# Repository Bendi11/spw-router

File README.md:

# 8 Port SpaceWire Router
A hobby-grade [SpaceWire](https://www.esa.int/Enabling_Support/Space_Engineering_Technology/Onboard_Computers_and_Data_Handling/SpaceWire) router
aiming for full **ECSS-E-ST-50-12C** compliance utilizing a Xilinx Artix 7 FPGA.

## Hardware Development
KiCad schematics and board design files for the board are stored in the `hw/board` directory.
Custom footprints and 3D models are placed into the `hw/models` directory.

## FPGA
Verilog sources are located in the `rtl/src` directory, and both the synthesis and simulation
processes are managed by CMake.

Currently, the FPGA bitstream is generated with a fully open-source
[yosys](https://github.com/YosysHQ/yosys) + [nextpnr-xilinx](https://github.com/gatecat/nextpnr-xilinx) flow,
and does not require the Xilinx Vivado software.
Paths to the required tools must currently be provided in an `env.cmake` file located in the
`rtl/cmake` directory, which must set the following:

| Variable Name | Description |
| :-----------: | ----------- |
| **YOSYS** | Path to the `yosys` binary |
| **NEXTPNR_XILINX** | Path to the `nextpnr-xilinx` binary, usually found at the root of the `nextpnr-xilinx` repository after building |
| **XRAY_DB_DIR** | Path to the Project X-Ray database |
| **XRAY_FASM2FRAMES** | Command to use the `fasm2frames` tool provided in Project X-Ray. This python script may have to run in Project X-Ray's virtual environment, so this variable is typically `"${PRJXRAY_DIR}/env/bin/python3" "${XRAY_DIR}/utils/fasm2frames.py"` |
| **XRAY_XC7FRAMES2BIT** | Path to the Project X-Ray's `xc7frames2bit` binary, usually in `${PRJXRAY_DIR}/build/tools/` |

### Example env.cmake
```cmake
set(NEXTPNR_XILINX_DIR "$ENV{HOME}/nextpnr-xilinx")
set(XRAY_DIR "$ENV{HOME}/prjxray")
set(XRAY_DB_DIR "${NEXTPNR_XILINX_DIR}/xilinx/external/prjxray-db")

set(YOSYS "yosys")
set(NEXTPNR_XILINX "${NEXTPNR_XILINX_DIR}/nextpnr-xilinx")
set(XRAY_FASM2FRAMES "${XRAY_DIR}/env/bin/python3" "${XRAY_DIR}/utils/fasm2frames.py")
set(XC7FRAMES2BIT "${XRAY_DIR}/build/tools/xc7frames2bit")
```

Design verification is performed with [Verilator](https://www.veripool.org/verilator/), with simulation
shims for Xilinx hard IP located in the `rtl/sim/verilog` directory.

## STM32 Software
`TODO`

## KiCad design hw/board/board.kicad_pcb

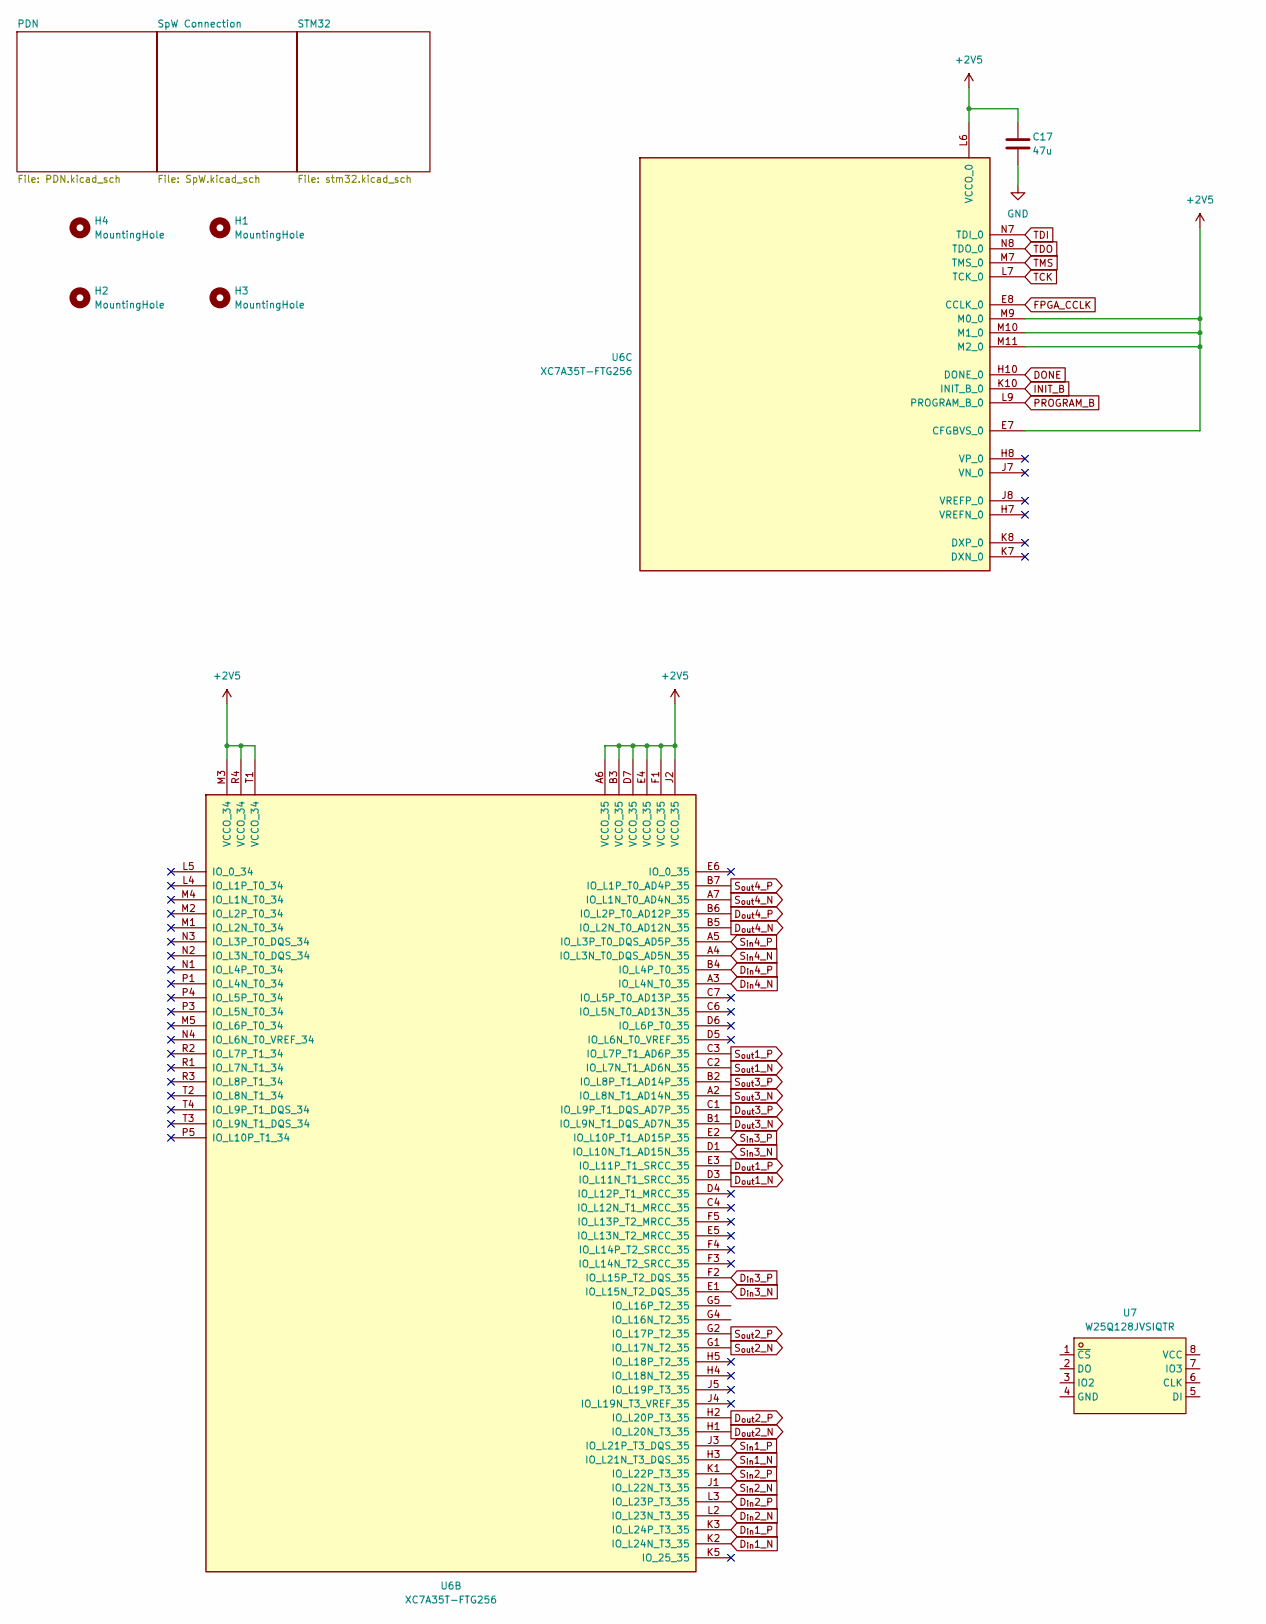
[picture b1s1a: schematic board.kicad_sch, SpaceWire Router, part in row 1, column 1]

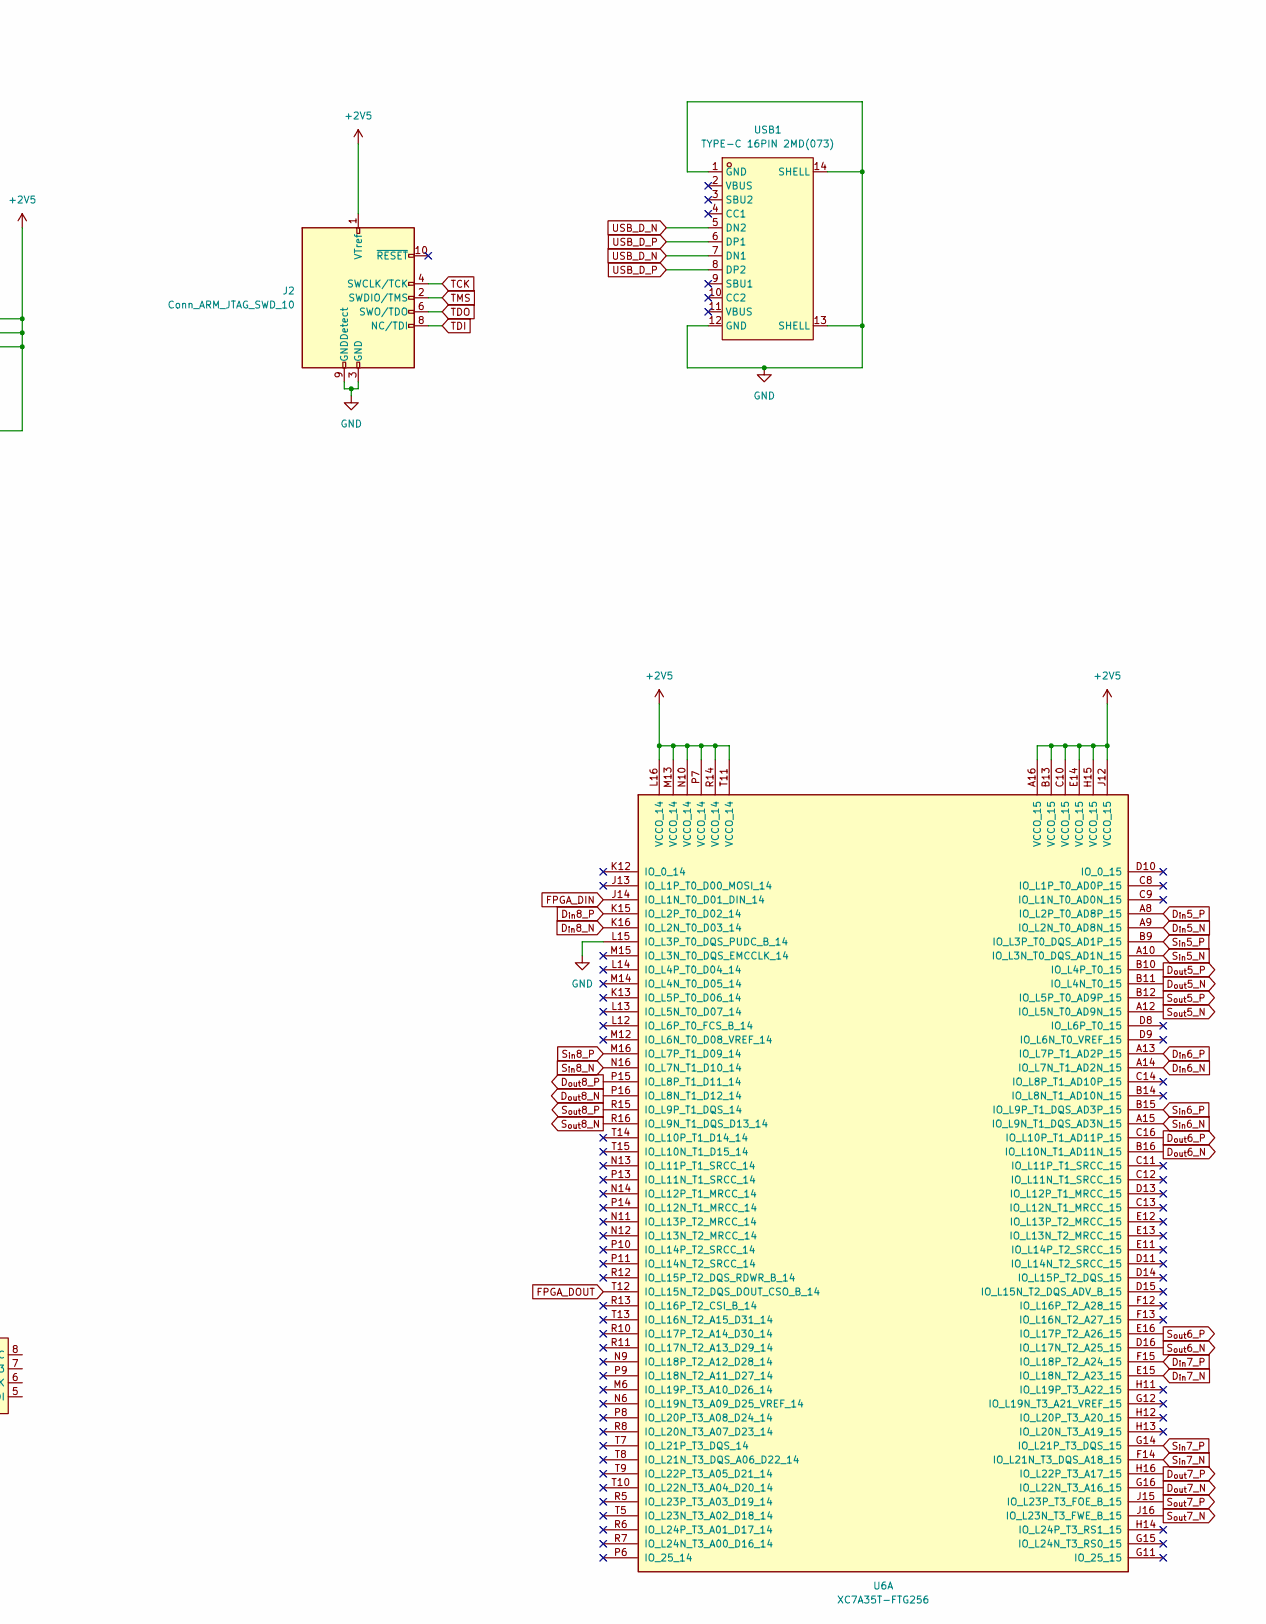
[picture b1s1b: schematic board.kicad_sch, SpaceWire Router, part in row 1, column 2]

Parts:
C17: 47u; C_0805_2012Metric
H1, H2, H3, H4: MountingHole; MountingHole_2.2mm_M2
J2: Conn_ARM_JTAG_SWD_10; PinHeader_2x05_P1.27mm_Vertical
U6: XC7A35T-FTG256; Xilinx_FTG256
U7: W25Q128JVSIQTR; SOIC-8_L5.3-W5.3-P1.27-LS8.0-BL; LCSC Part C97521
USB1: TYPE-C 16PIN 2MD(073); USB-C-SMD_TYPE-C-6PIN-2MD-073; LCSC Part C2765186

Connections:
+2V5: C17.1, J2.1 (VTref), U6.A6 (VCCO_35), U6.A16 (VCCO_15), U6.B3 (VCCO_35), U6.B13 (VCCO_15), U6.C10 (VCCO_15), U6.D7 (VCCO_35), U6.E4 (VCCO_35), U6.E7 (CFGBVS_0), U6.E14 (VCCO_15), U6.F1 (VCCO_35), U6.H15 (VCCO_15), U6.J2 (VCCO_35), U6.J12 (VCCO_15), U6.L6 (VCCO_0), U6.L16 (VCCO_14), U6.M3 (VCCO_34), U6.M9 (M0_0), U6.M10 (M1_0), U6.M11 (M2_0), U6.M13 (VCCO_14), U6.N10 (VCCO_14), U6.P7 (VCCO_14), U6.R4 (VCCO_34), U6.R14 (VCCO_14), U6.T1 (VCCO_34), U6.T11 (VCCO_14); also elsewhere on the board
DONE: U6.H10 (DONE_0); also elsewhere on the board
D_{in}1_N: U6.K2 (IO_L24N_T3_35); also elsewhere on the board
D_{in}1_P: U6.K3 (IO_L24P_T3_35); also elsewhere on the board
D_{in}2_N: U6.L2 (IO_L23N_T3_35); also elsewhere on the board
D_{in}2_P: U6.L3 (IO_L23P_T3_35); also elsewhere on the board
D_{in}3_N: U6.E1 (IO_L15N_T2_DQS_35); also elsewhere on the board
D_{in}3_P: U6.F2 (IO_L15P_T2_DQS_35); also elsewhere on the board
D_{in}4_N: U6.A3 (IO_L4N_T0_35); also elsewhere on the board
D_{in}4_P: U6.B4 (IO_L4P_T0_35); also elsewhere on the board
D_{in}5_N: U6.A9 (IO_L2N_T0_AD8N_15); also elsewhere on the board
D_{in}5_P: U6.A8 (IO_L2P_T0_AD8P_15); also elsewhere on the board
D_{in}6_N: U6.A14 (IO_L7N_T1_AD2N_15); also elsewhere on the board
D_{in}6_P: U6.A13 (IO_L7P_T1_AD2P_15); also elsewhere on the board
D_{in}7_N: U6.E15 (IO_L18N_T2_A23_15); also elsewhere on the board
D_{in}7_P: U6.F15 (IO_L18P_T2_A24_15); also elsewhere on the board
D_{in}8_N: U6.K16 (IO_L2N_T0_D03_14); also elsewhere on the board
D_{in}8_P: U6.K15 (IO_L2P_T0_D02_14); also elsewhere on the board
D_{out}1_N: U6.D3 (IO_L11N_T1_SRCC_35); also elsewhere on the board
D_{out}1_P: U6.E3 (IO_L11P_T1_SRCC_35); also elsewhere on the board
D_{out}2_N: U6.H1 (IO_L20N_T3_35); also elsewhere on the board
D_{out}2_P: U6.H2 (IO_L20P_T3_35); also elsewhere on the board
D_{out}3_N: U6.B1 (IO_L9N_T1_DQS_AD7N_35); also elsewhere on the board
D_{out}3_P: U6.C1 (IO_L9P_T1_DQS_AD7P_35); also elsewhere on the board
D_{out}4_N: U6.B5 (IO_L2N_T0_AD12N_35); also elsewhere on the board
D_{out}4_P: U6.B6 (IO_L2P_T0_AD12P_35); also elsewhere on the board
D_{out}5_N: U6.B11 (IO_L4N_T0_15); also elsewhere on the board
D_{out}5_P: U6.B10 (IO_L4P_T0_15); also elsewhere on the board
D_{out}6_N: U6.B16 (IO_L10N_T1_AD11N_15); also elsewhere on the board
D_{out}6_P: U6.C16 (IO_L10P_T1_AD11P_15); also elsewhere on the board
D_{out}7_N: U6.G16 (IO_L22N_T3_A16_15); also elsewhere on the board
D_{out}7_P: U6.H16 (IO_L22P_T3_A17_15); also elsewhere on the board
D_{out}8_N: U6.P16 (IO_L8N_T1_D12_14); also elsewhere on the board
D_{out}8_P: U6.P15 (IO_L8P_T1_D11_14); also elsewhere on the board
FPGA_CCLK: U6.E8 (CCLK_0); also elsewhere on the board
FPGA_DIN: U6.J14 (IO_L1N_T0_D01_DIN_14); also elsewhere on the board
FPGA_DOUT: U6.T12 (IO_L15N_T2_DQS_DOUT_CSO_B_14); also elsewhere on the board
GND: C17.2, J2.3 (GND), J2.5 (GND), J2.9 (GNDDetect), U6.L15 (IO_L3P_T0_DQS_PUDC_B_14), USB1.1 (GND), USB1.12 (GND), USB1.13 (SHELL), USB1.14 (SHELL); also elsewhere on the board
INIT_B: U6.K10 (INIT_B_0); also elsewhere on the board
PROGRAM_B: U6.L9 (PROGRAM_B_0); also elsewhere on the board
S_{in}1_N: U6.H3 (IO_L21N_T3_DQS_35); also elsewhere on the board
S_{in}1_P: U6.J3 (IO_L21P_T3_DQS_35); also elsewhere on the board
S_{in}2_N: U6.J1 (IO_L22N_T3_35); also elsewhere on the board
S_{in}2_P: U6.K1 (IO_L22P_T3_35); also elsewhere on the board
S_{in}3_N: U6.D1 (IO_L10N_T1_AD15N_35); also elsewhere on the board
S_{in}3_P: U6.E2 (IO_L10P_T1_AD15P_35); also elsewhere on the board
S_{in}4_N: U6.A4 (IO_L3N_T0_DQS_AD5N_35); also elsewhere on the board
S_{in}4_P: U6.A5 (IO_L3P_T0_DQS_AD5P_35); also elsewhere on the board
S_{in}5_N: U6.A10 (IO_L3N_T0_DQS_AD1N_15); also elsewhere on the board
S_{in}5_P: U6.B9 (IO_L3P_T0_DQS_AD1P_15); also elsewhere on the board
S_{in}6_N: U6.A15 (IO_L9N_T1_DQS_AD3N_15); also elsewhere on the board
S_{in}6_P: U6.B15 (IO_L9P_T1_DQS_AD3P_15); also elsewhere on the board
S_{in}7_N: U6.F14 (IO_L21N_T3_DQS_A18_15); also elsewhere on the board
S_{in}7_P: U6.G14 (IO_L21P_T3_DQS_15); also elsewhere on the board
S_{in}8_N: U6.N16 (IO_L7N_T1_D10_14); also elsewhere on the board
S_{in}8_P: U6.M16 (IO_L7P_T1_D09_14); also elsewhere on the board
S_{out}1_N: U6.C2 (IO_L7N_T1_AD6N_35); also elsewhere on the board
S_{out}1_P: U6.C3 (IO_L7P_T1_AD6P_35); also elsewhere on the board
S_{out}2_N: U6.G1 (IO_L17N_T2_35); also elsewhere on the board
S_{out}2_P: U6.G2 (IO_L17P_T2_35); also elsewhere on the board
S_{out}3_N: U6.A2 (IO_L8N_T1_AD14N_35); also elsewhere on the board
S_{out}3_P: U6.B2 (IO_L8P_T1_AD14P_35); also elsewhere on the board
S_{out}4_N: U6.A7 (IO_L1N_T0_AD4N_35); also elsewhere on the board
S_{out}4_P: U6.B7 (IO_L1P_T0_AD4P_35); also elsewhere on the board
S_{out}5_N: U6.A12 (IO_L5N_T0_AD9N_15); also elsewhere on the board
S_{out}5_P: U6.B12 (IO_L5P_T0_AD9P_15); also elsewhere on the board
S_{out}6_N: U6.D16 (IO_L17N_T2_A25_15); also elsewhere on the board
S_{out}6_P: U6.E16 (IO_L17P_T2_A26_15); also elsewhere on the board
S_{out}7_N: U6.J16 (IO_L23N_T3_FWE_B_15); also elsewhere on the board
S_{out}7_P: U6.J15 (IO_L23P_T3_FOE_B_15); also elsewhere on the board
S_{out}8_N: U6.R16 (IO_L9N_T1_DQS_D13_14); also elsewhere on the board
S_{out}8_P: U6.R15 (IO_L9P_T1_DQS_14); also elsewhere on the board
TCK: J2.4 (SWCLK/TCK), U6.L7 (TCK_0)
TDI: J2.8 (NC/TDI), U6.N7 (TDI_0)
TDO: J2.6 (SWO/TDO), U6.N8 (TDO_0)
TMS: J2.2 (SWDIO/TMS), U6.M7 (TMS_0)
USB_D_N: USB1.5 (DN2), USB1.7 (DN1); also elsewhere on the board
USB_D_P: USB1.6 (DP1), USB1.8 (DP2); also elsewhere on the board

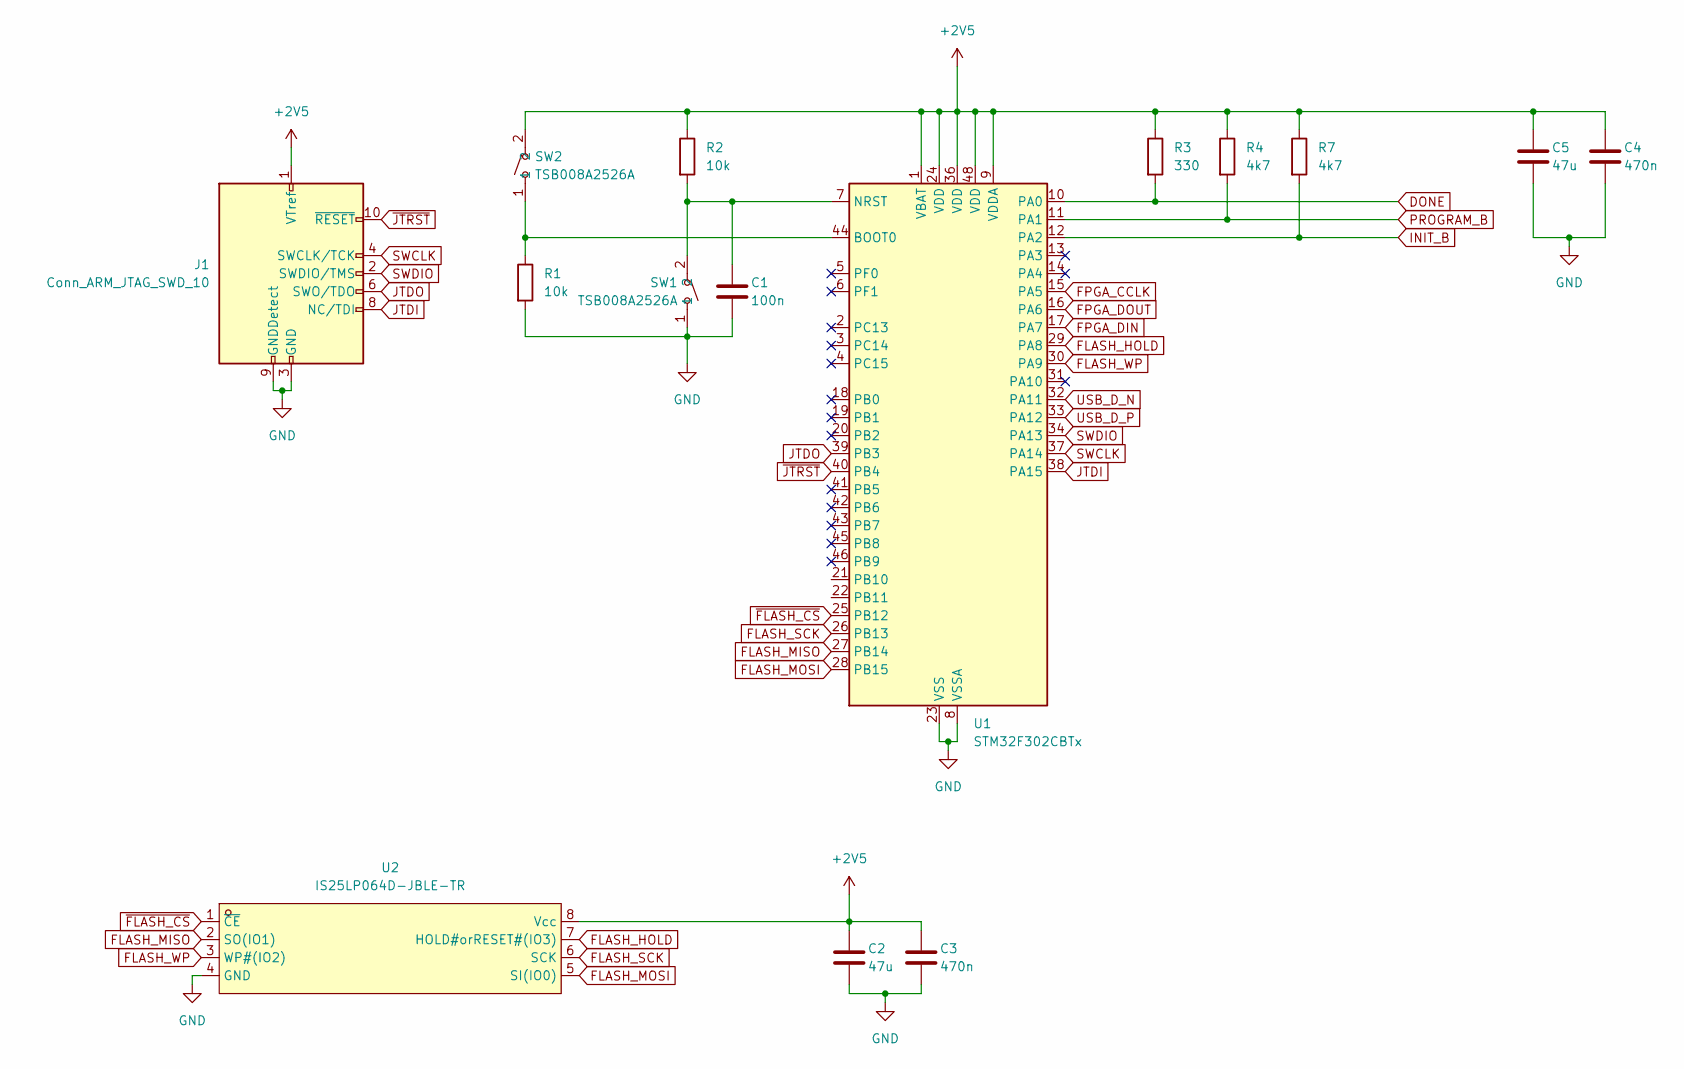
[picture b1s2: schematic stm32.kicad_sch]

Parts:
C1: 100n; C_0805_2012Metric
C2, C5: 47u; C_0805_2012Metric
C3, C4: 470n; C_0805_2012Metric
J1: Conn_ARM_JTAG_SWD_10; PinHeader_2x05_P1.27mm_Vertical
R1, R2: 10k; R_0805_2012Metric
R3: 330; R_0805_2012Metric
R4, R7: 4k7; R_0805_2012Metric
SW1, SW2: TSB008A2526A; SW-SMD_L6.0-W3.5-LS8.0; LCSC Part C2888456
U1: STM32F302CBTx; LQFP-48_7x7mm_P0.5mm
U2: IS25LP064D-JBLE-TR; SOIC-8_L5.3-W5.3-P1.27-LS7.9-BL; LCSC Part C5183018

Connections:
+2V5: C2.1, C3.1, C4.1, C5.1, J1.1 (VTref), R2.1, R3.1, R4.1, R7.1, SW2.2, U1.1 (VBAT), U1.9 (VDDA), U1.24 (VDD), U1.36 (VDD), U1.48 (VDD), U2.8 (Vcc); also elsewhere on the board
DONE: R3.2, U1.10 (PA0); also elsewhere on the board
FLASH_HOLD: U1.29 (PA8), U2.7 (HOLD#orRESET#(IO3))
FLASH_MISO: U1.27 (PB14), U2.2 (SO(IO1))
FLASH_MOSI: U1.28 (PB15), U2.5 (SI(IO0))
FLASH_SCK: U1.26 (PB13), U2.6 (SCK)
FLASH_WP: U1.30 (PA9), U2.3 (WP#(IO2))
FPGA_CCLK: U1.15 (PA5); also elsewhere on the board
FPGA_DIN: U1.17 (PA7); also elsewhere on the board
FPGA_DOUT: U1.16 (PA6); also elsewhere on the board
GND: C1.2, C2.2, C3.2, C4.2, C5.2, J1.3 (GND), J1.5 (GND), J1.9 (GNDDetect), R1.2, SW1.1, U1.8 (VSSA), U1.23 (VSS), U1.35 (VSS), U1.47 (VSS), U2.4 (GND); also elsewhere on the board
INIT_B: R7.2, U1.12 (PA2); also elsewhere on the board
JTDI: J1.8 (NC/TDI), U1.38 (PA15)
JTDO: J1.6 (SWO/TDO), U1.39 (PB3)
unnamed: R1.1, SW2.1, U1.44 (BOOT0)
unnamed: C1.1, R2.2, SW1.2, U1.7 (NRST)
PROGRAM_B: R4.2, U1.11 (PA1); also elsewhere on the board
SWCLK: J1.4 (SWCLK/TCK), U1.37 (PA14)
SWDIO: J1.2 (SWDIO/TMS), U1.34 (PA13)
USB_D_N: U1.32 (PA11); also elsewhere on the board
USB_D_P: U1.33 (PA12); also elsewhere on the board
~FLASH_CS: U1.25 (PB12), U2.1 (~CE)
~JTRST: J1.10 (~RESET), U1.40 (PB4)

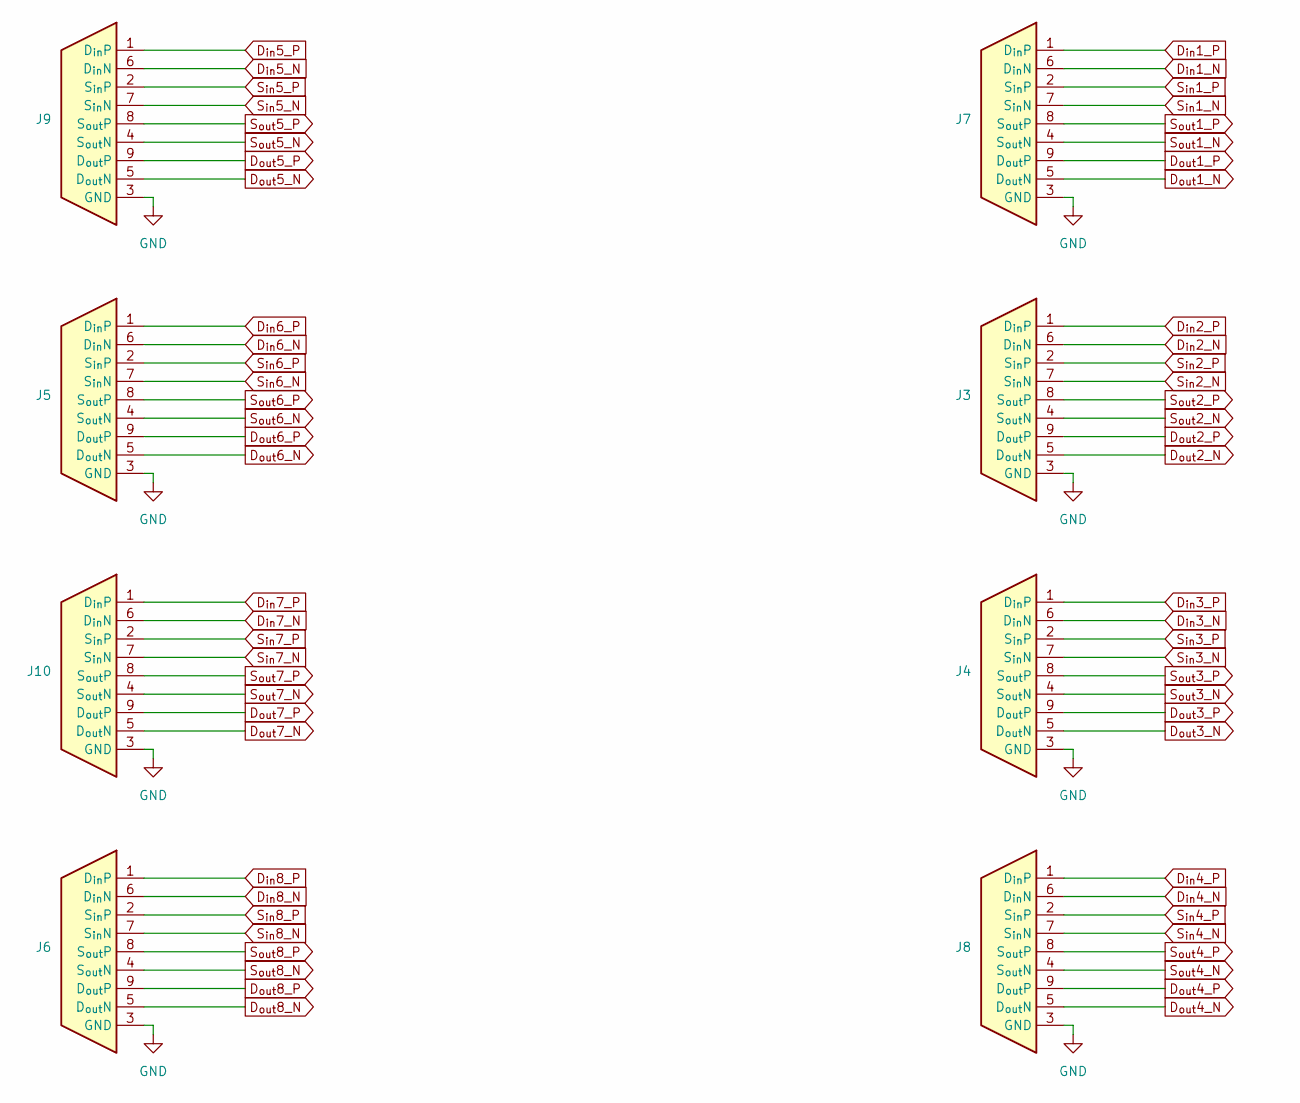
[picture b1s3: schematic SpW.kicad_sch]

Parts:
J3, J4, J5, J6, J7, J8, J9, J10: DE9_Pins

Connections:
D_{in}1_N: J7.6 (D_{in}N); also elsewhere on the board
D_{in}1_P: J7.1 (D_{in}P); also elsewhere on the board
D_{in}2_N: J3.6 (D_{in}N); also elsewhere on the board
D_{in}2_P: J3.1 (D_{in}P); also elsewhere on the board
D_{in}3_N: J4.6 (D_{in}N); also elsewhere on the board
D_{in}3_P: J4.1 (D_{in}P); also elsewhere on the board
D_{in}4_N: J8.6 (D_{in}N); also elsewhere on the board
D_{in}4_P: J8.1 (D_{in}P); also elsewhere on the board
D_{in}5_N: J9.6 (D_{in}N); also elsewhere on the board
D_{in}5_P: J9.1 (D_{in}P); also elsewhere on the board
D_{in}6_N: J5.6 (D_{in}N); also elsewhere on the board
D_{in}6_P: J5.1 (D_{in}P); also elsewhere on the board
D_{in}7_N: J10.6 (D_{in}N); also elsewhere on the board
D_{in}7_P: J10.1 (D_{in}P); also elsewhere on the board
D_{in}8_N: J6.6 (D_{in}N); also elsewhere on the board
D_{in}8_P: J6.1 (D_{in}P); also elsewhere on the board
D_{out}1_N: J7.5 (D_{out}N); also elsewhere on the board
D_{out}1_P: J7.9 (D_{out}P); also elsewhere on the board
D_{out}2_N: J3.5 (D_{out}N); also elsewhere on the board
D_{out}2_P: J3.9 (D_{out}P); also elsewhere on the board
D_{out}3_N: J4.5 (D_{out}N); also elsewhere on the board
D_{out}3_P: J4.9 (D_{out}P); also elsewhere on the board
D_{out}4_N: J8.5 (D_{out}N); also elsewhere on the board
D_{out}4_P: J8.9 (D_{out}P); also elsewhere on the board
D_{out}5_N: J9.5 (D_{out}N); also elsewhere on the board
D_{out}5_P: J9.9 (D_{out}P); also elsewhere on the board
D_{out}6_N: J5.5 (D_{out}N); also elsewhere on the board
D_{out}6_P: J5.9 (D_{out}P); also elsewhere on the board
D_{out}7_N: J10.5 (D_{out}N); also elsewhere on the board
D_{out}7_P: J10.9 (D_{out}P); also elsewhere on the board
D_{out}8_N: J6.5 (D_{out}N); also elsewhere on the board
D_{out}8_P: J6.9 (D_{out}P); also elsewhere on the board
GND: J3.3 (GND), J4.3 (GND), J5.3 (GND), J6.3 (GND), J7.3 (GND), J8.3 (GND), J9.3 (GND), J10.3 (GND); also elsewhere on the board
S_{in}1_N: J7.7 (S_{in}N); also elsewhere on the board
S_{in}1_P: J7.2 (S_{in}P); also elsewhere on the board
S_{in}2_N: J3.7 (S_{in}N); also elsewhere on the board
S_{in}2_P: J3.2 (S_{in}P); also elsewhere on the board
S_{in}3_N: J4.7 (S_{in}N); also elsewhere on the board
S_{in}3_P: J4.2 (S_{in}P); also elsewhere on the board
S_{in}4_N: J8.7 (S_{in}N); also elsewhere on the board
S_{in}4_P: J8.2 (S_{in}P); also elsewhere on the board
S_{in}5_N: J9.7 (S_{in}N); also elsewhere on the board
S_{in}5_P: J9.2 (S_{in}P); also elsewhere on the board
S_{in}6_N: J5.7 (S_{in}N); also elsewhere on the board
S_{in}6_P: J5.2 (S_{in}P); also elsewhere on the board
S_{in}7_N: J10.7 (S_{in}N); also elsewhere on the board
S_{in}7_P: J10.2 (S_{in}P); also elsewhere on the board
S_{in}8_N: J6.7 (S_{in}N); also elsewhere on the board
S_{in}8_P: J6.2 (S_{in}P); also elsewhere on the board
S_{out}1_N: J7.4 (S_{out}N); also elsewhere on the board
S_{out}1_P: J7.8 (S_{out}P); also elsewhere on the board
S_{out}2_N: J3.4 (S_{out}N); also elsewhere on the board
S_{out}2_P: J3.8 (S_{out}P); also elsewhere on the board
S_{out}3_N: J4.4 (S_{out}N); also elsewhere on the board
S_{out}3_P: J4.8 (S_{out}P); also elsewhere on the board
S_{out}4_N: J8.4 (S_{out}N); also elsewhere on the board
S_{out}4_P: J8.8 (S_{out}P); also elsewhere on the board
S_{out}5_N: J9.4 (S_{out}N); also elsewhere on the board
S_{out}5_P: J9.8 (S_{out}P); also elsewhere on the board
S_{out}6_N: J5.4 (S_{out}N); also elsewhere on the board
S_{out}6_P: J5.8 (S_{out}P); also elsewhere on the board
S_{out}7_N: J10.4 (S_{out}N); also elsewhere on the board
S_{out}7_P: J10.8 (S_{out}P); also elsewhere on the board
S_{out}8_N: J6.4 (S_{out}N); also elsewhere on the board
S_{out}8_P: J6.8 (S_{out}P); also elsewhere on the board

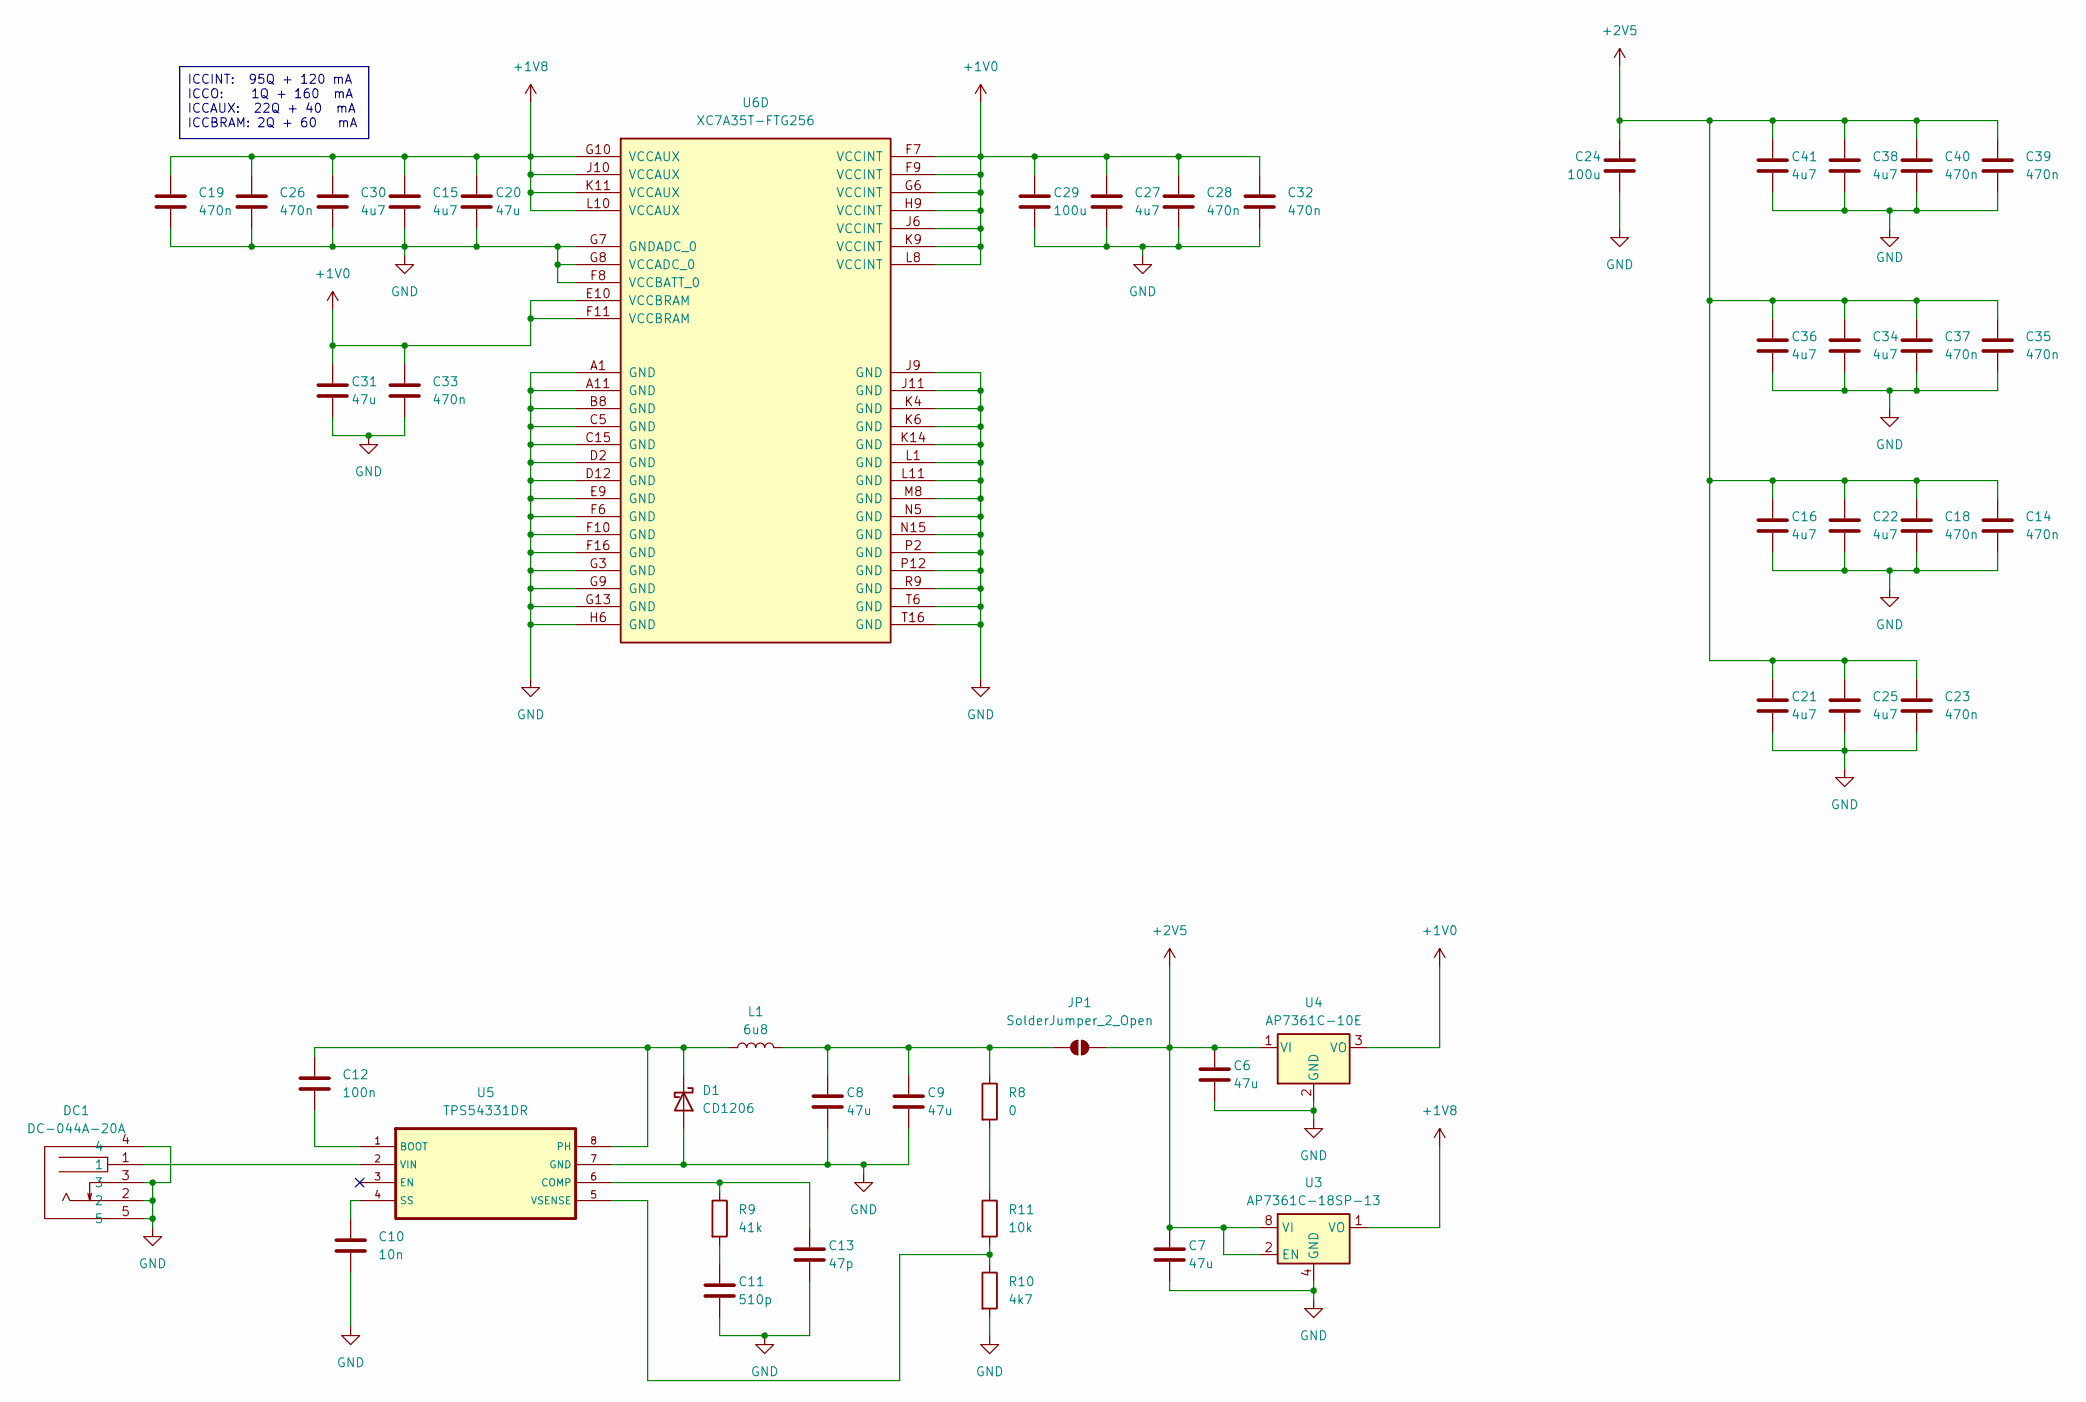
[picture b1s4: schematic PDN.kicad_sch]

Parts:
C6, C7, C8, C9, C20, C31: 47u; C_0805_2012Metric
C10: 10n; C_0805_2012Metric
C11: 510p; C_0805_2012Metric
C12: 100n; C_0805_2012Metric
C13: 47p; C_0805_2012Metric
C14, C18, C19, C23, C26, C28, C32, C33, C35, C37, C39, C40: 470n; C_0805_2012Metric
C15, C16, C21, C22, C25, C27, C30, C34, C36, C38, C41: 4u7; C_0805_2012Metric
C24, C29: 100u; C_0805_2012Metric
D1: CD1206; D_1206_3216Metric
DC1: DC-044A-20A; DC-IN-TH_DC-044A-20A; LCSC Part C129006
JP1: SolderJumper_2_Open; SolderJumper-2_P1.3mm_Open_TrianglePad1.0x1.5mm
L1: 6u8; IND-SMD_L11.6-W10.1
R8: 0; R_0805_2012Metric
R9: 41k; R_0805_2012Metric
R10: 4k7; R_0805_2012Metric
R11: 10k; R_0805_2012Metric
U3: AP7361C-18SP-13; SOIC-8-1EP_3.9x4.9mm_P1.27mm_EP2.41x3.3mm_ThermalVias
U4: AP7361C-10E; SOT-223-3_TabPin2
U5: TPS54331DR; SOIC127P599X175-8N
U6: XC7A35T-FTG256; Xilinx_FTG256

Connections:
+1V0: C27.1, C28.1, C29.1, C31.1, C32.1, C33.1, U4.3 (VO), U6.E10 (VCCBRAM), U6.F7 (VCCINT), U6.F9 (VCCINT), U6.F11 (VCCBRAM), U6.G6 (VCCINT), U6.H9 (VCCINT), U6.J6 (VCCINT), U6.K9 (VCCINT), U6.L8 (VCCINT)
+1V8: C15.1, C19.1, C20.1, C26.1, C30.1, U3.1 (VO), U6.G10 (VCCAUX), U6.J10 (VCCAUX), U6.K11 (VCCAUX), U6.L10 (VCCAUX)
+2V5: C6.1, C7.1, C14.1, C16.1, C18.1, C21.1, C22.1, C23.1, C24.1, C25.1, C34.1, C35.1, C36.1, C37.1, C38.1, C39.1, C40.1, C41.1, JP1.2 (B), U3.2 (EN), U3.8 (VI), U4.1 (VI); also elsewhere on the board
GND: C6.2, C7.2, C8.2, C9.2, C10.2, C11.2, C13.2, C14.2, C15.2, C16.2, C18.2, C19.2, C20.2, C21.2, C22.2, C23.2, C24.2, C25.2, C26.2, C27.2, C28.2, C29.2, C30.2, C31.2, C32.2, C33.2, C34.2, C35.2, C36.2, C37.2, C38.2, C39.2, C40.2, C41.2, D1.2 (A), DC1.2, DC1.3, DC1.4, DC1.5, R10.2, U3.4 (GND), U4.2 (GND), U5.7 (GND), U6.A1 (GND), U6.A11 (GND), U6.B8 (GND), U6.C5 (GND), U6.C15 (GND), U6.D2 (GND), U6.D12 (GND), U6.E9 (GND), U6.F6 (GND), U6.F8 (VCCBATT_0), U6.F10 (GND), U6.F16 (GND), U6.G3 (GND), U6.G7 (GNDADC_0), U6.G8 (VCCADC_0), U6.G9 (GND), U6.G13 (GND), U6.H6 (GND), U6.J9 (GND), U6.J11 (GND), U6.K4 (GND), U6.K6 (GND), U6.K14 (GND), U6.L1 (GND), U6.L11 (GND), U6.M8 (GND), U6.N5 (GND), U6.N15 (GND), U6.P2 (GND), U6.P12 (GND), U6.R9 (GND), U6.T6 (GND), U6.T16 (GND); also elsewhere on the board
unnamed: C11.1, R9.2
unnamed: C12.1, D1.1 (K), L1.1, U5.8 (PH)
unnamed: C8.1, C9.1, JP1.1 (A), L1.2, R8.1
unnamed: R8.2, R11.1
unnamed: C12.2, U5.1 (BOOT)
unnamed: C13.1, R9.1, U5.6 (COMP)
unnamed: C10.1, U5.4 (SS)
unnamed: DC1.1, U5.2 (VIN)
unnamed: R10.1, R11.2, U5.5 (VSENSE)

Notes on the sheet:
ICCINT: 95Q + 120 mA ICCO: 1Q + 160 mA ICCAUX: 22Q + 40 mA ICCBRAM: 2Q + 60 mA

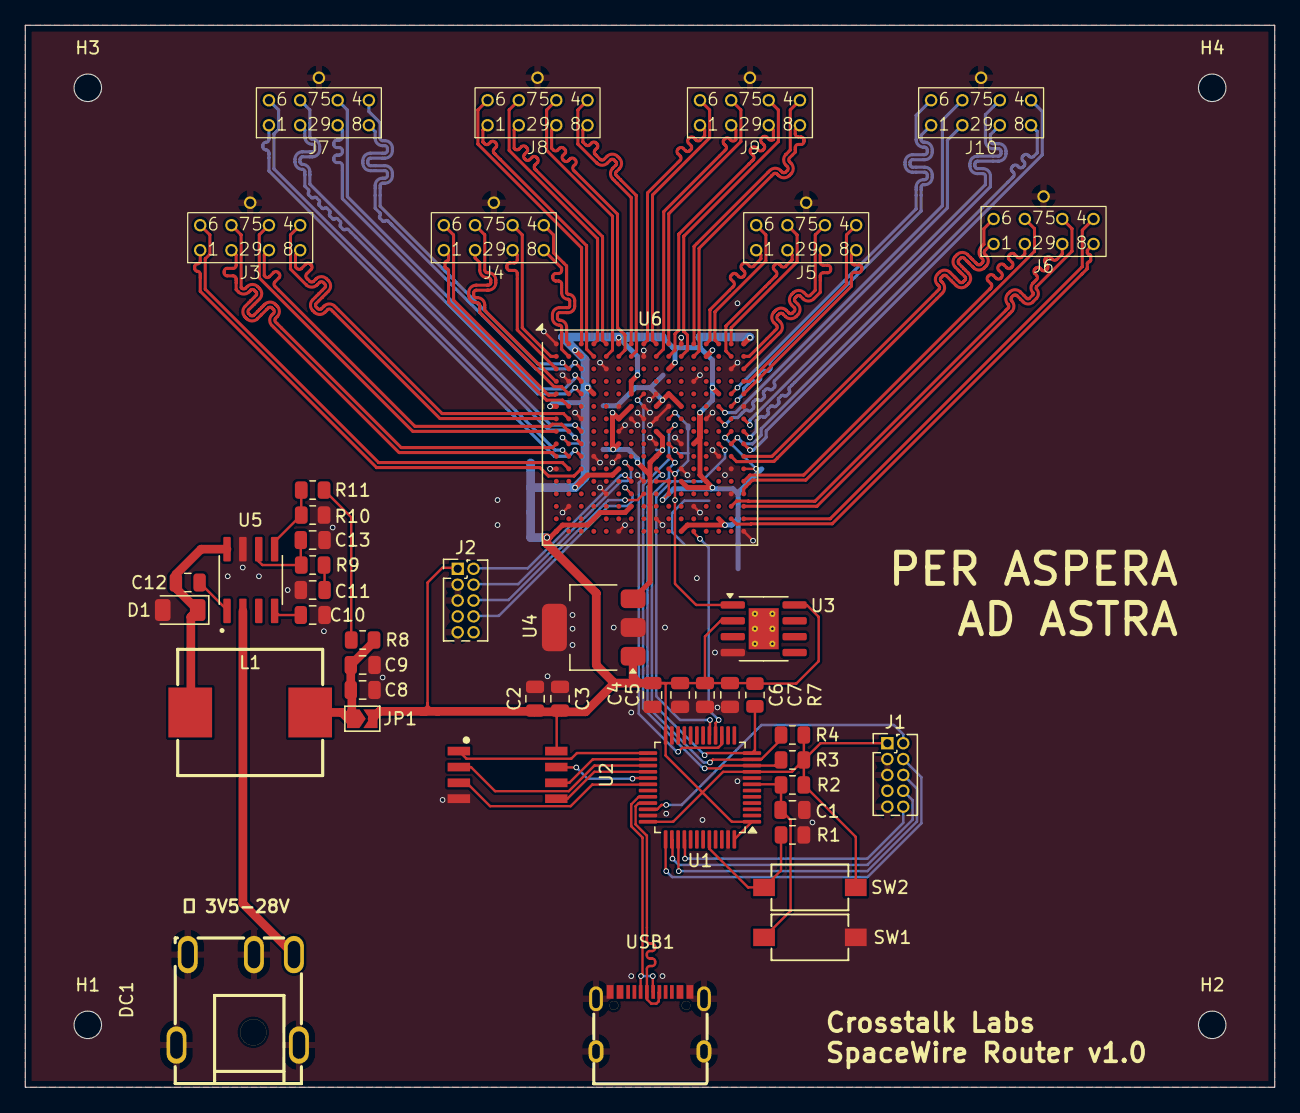
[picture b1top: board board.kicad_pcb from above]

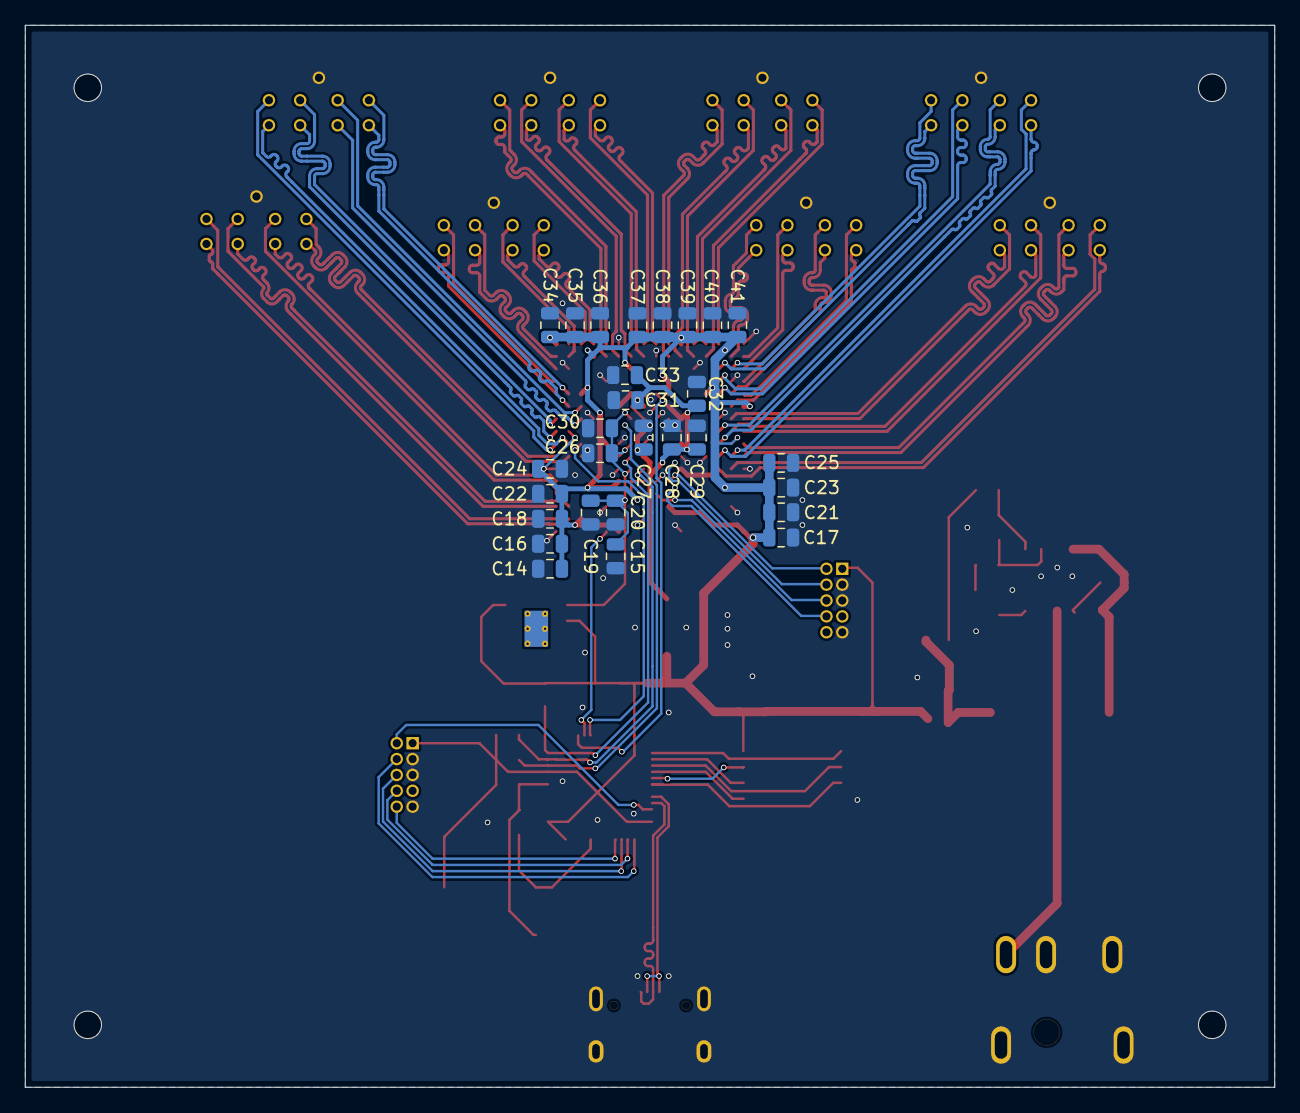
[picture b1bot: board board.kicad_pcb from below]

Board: 4 copper layers, 100.0 x 85.0 mm, 77 parts (28 on the bottom side), 102 nets.
